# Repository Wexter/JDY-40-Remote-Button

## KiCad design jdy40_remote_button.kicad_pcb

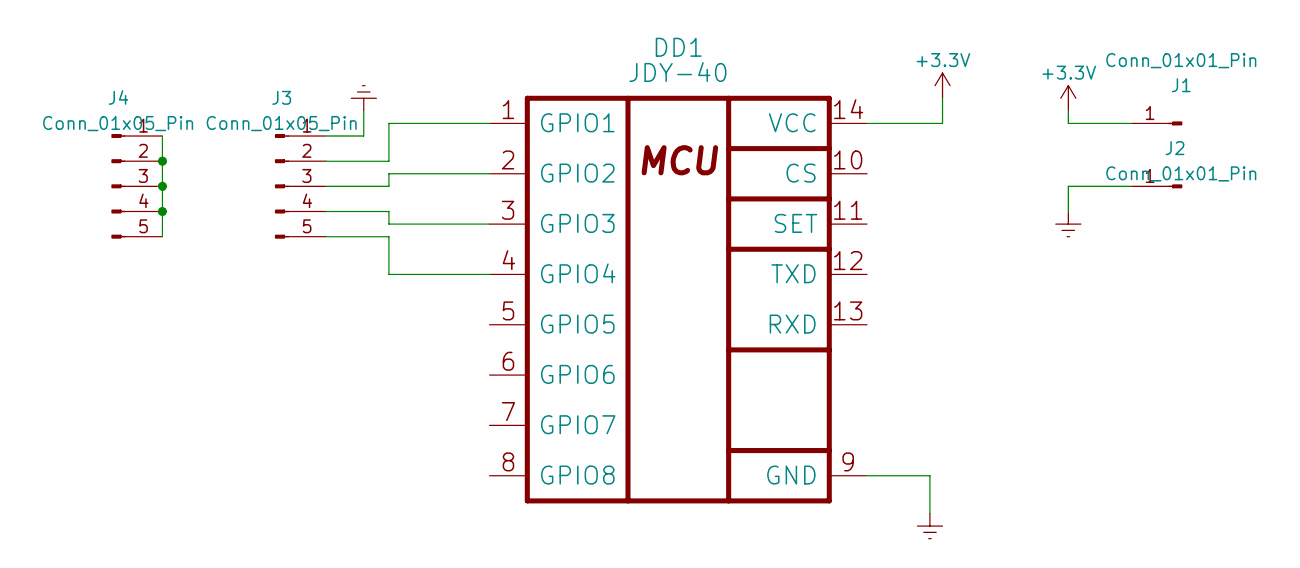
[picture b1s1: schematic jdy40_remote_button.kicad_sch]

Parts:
DD1: JDY-40; JDY40
J1: Conn_01x01_Pin; PinHeader_1x01_P2.54mm_Vertical
J2: Conn_01x01_Pin; PinHeader_1x01_P2.54mm_Horizontal
J3, J4: Conn_01x05_Pin; PinHeader_1x05_P2.54mm_Vertical

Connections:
+3.3V: DD1.14 (VCC), J1.1
Earth: DD1.9 (GND), J2.1, J3.1
unnamed: DD1.1 (GPIO1), J3.2
unnamed: DD1.2 (GPIO2), J3.3
unnamed: DD1.3 (GPIO3), J3.4
unnamed: DD1.4 (GPIO4), J3.5
unnamed: J4.1, J4.2, J4.3, J4.4, J4.5

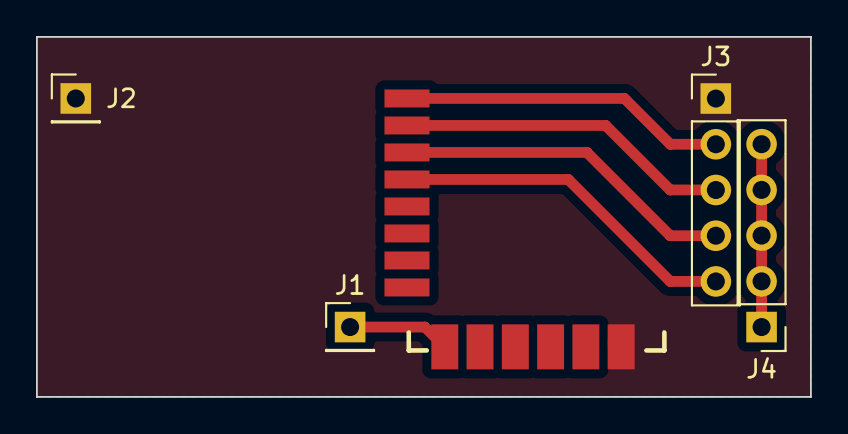
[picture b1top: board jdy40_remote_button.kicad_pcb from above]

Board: 2 copper layers, 43.0 x 20.0 mm, 5 parts (0 on the bottom side), 7 nets.

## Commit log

2024-02-11 Rev 0.1
